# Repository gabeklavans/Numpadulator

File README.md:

# Numpadulator
 QMK powered numpad + calculator
 
 ## TODO:
 * Write (or borrow) C calculator code
 * Incorporate calculator into Numpadulator
 * ~~Build working prototype~~

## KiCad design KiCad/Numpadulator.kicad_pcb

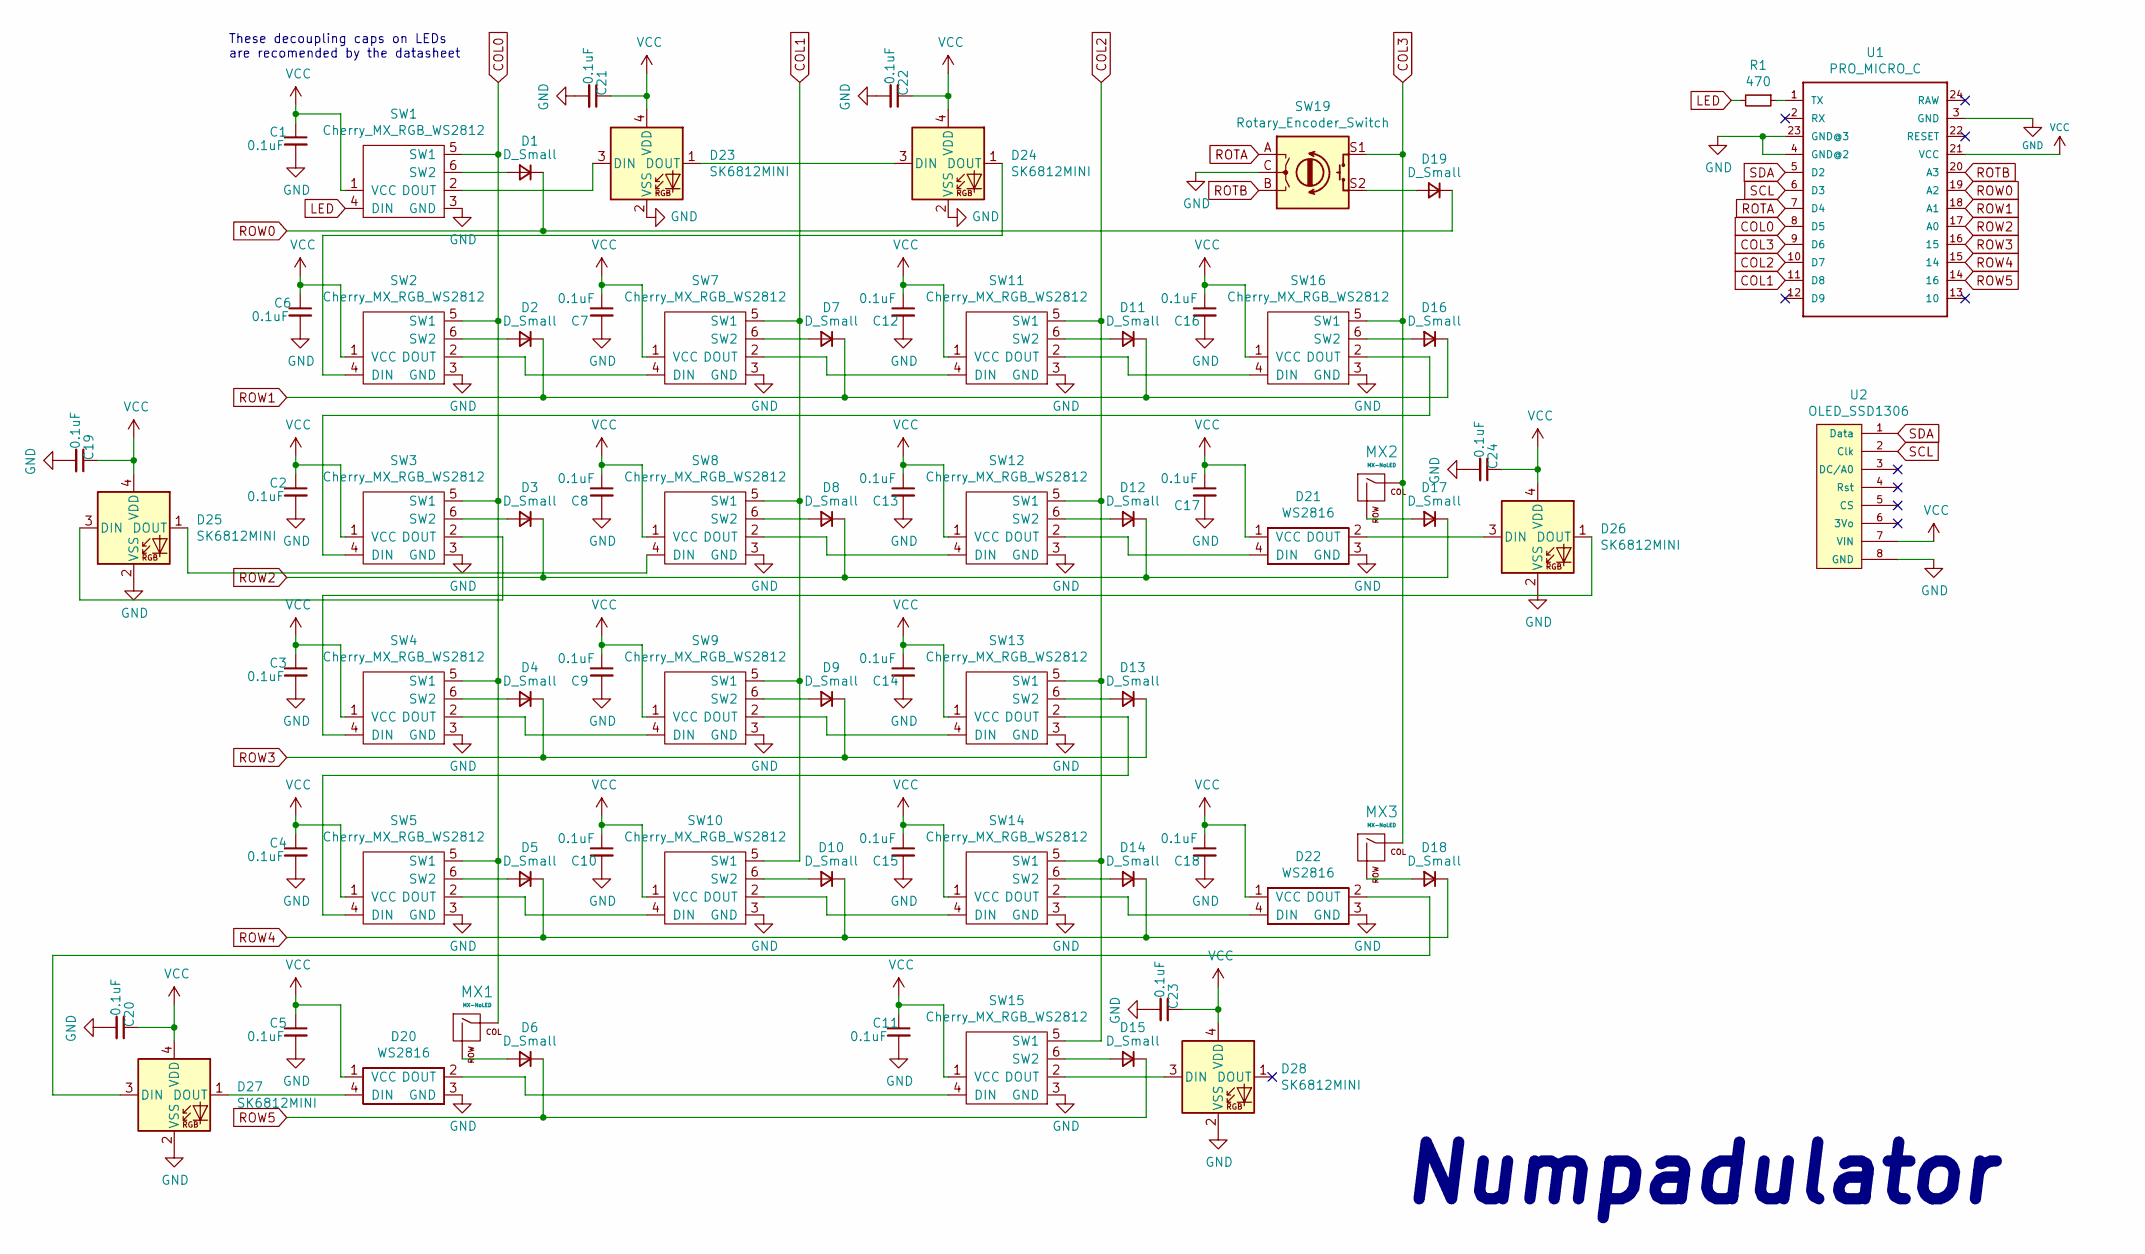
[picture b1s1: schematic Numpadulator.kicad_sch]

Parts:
C1, C2, C3, C4, C5, C6, C7, C8, C9, C10, C11, C12, C13, C14, C15, C16, C17, C18, C19, C20, C21, C22, C23, C24: 0.1uF; C_0805_2012Metric
D1, D2, D3, D4, D5, D6, D7, D8, D9, D10, D11, D12, D13, D14, D15, D16, D17, D18, D19: D_Small; D_SOD-123
D20, D21, D22: WS2816; SK6812-MINI-E
D23, D24, D25, D26, D27, D28: SK6812MINI; LED_SK6812MINI_PLCC4_3.5x3.5mm_P1.75mm
MX1, MX2, MX3: MX-NoLED; MXOnly-2U-Hotswap
R1: 470; R_0805_2012Metric
SW1, SW2, SW3, SW4, SW5, SW7, SW8, SW9, SW10, SW11, SW12, SW13, SW14, SW15, SW16: Cherry_MX_RGB_WS2812; Cherry-MX_PCB-Mounted_SK6812-MINI-E_Kailh_Socket
SW19: Rotary_Encoder_Switch; XDCR_PEC11R-4215F-S0024
U1: PRO_MICRO_C
U2: OLED_SSD1306; Adafruit_SSD1306

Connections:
COL0: MX1.1 (COL), SW1.5 (SW1), SW2.5 (SW1), SW3.5 (SW1), SW4.5 (SW1), SW5.5 (SW1), U1.8 (D5)
COL1: SW7.5 (SW1), SW8.5 (SW1), SW9.5 (SW1), SW10.5 (SW1), U1.11 (D8)
COL2: SW11.5 (SW1), SW12.5 (SW1), SW13.5 (SW1), SW14.5 (SW1), SW15.5 (SW1), U1.10 (D7)
COL3: MX2.1 (COL), MX3.1 (COL), SW16.5 (SW1), SW19.S1, U1.9 (D6)
GND: C1.2, C2.2, C3.2, C4.2, C5.2, C6.2, C7.2, C8.2, C9.2, C10.2, C11.2, C12.2, C13.2, C14.2, C15.2, C16.2, C17.2, C18.2, C19.2, C20.2, C21.2, C22.2, C23.2, C24.2, D20.3 (GND), D21.3 (GND), D22.3 (GND), D23.2 (VSS), D24.2 (VSS), D25.2 (VSS), D26.2 (VSS), D27.2 (VSS), D28.2 (VSS), SW1.3 (GND), SW2.3 (GND), SW3.3 (GND), SW4.3 (GND), SW5.3 (GND), SW7.3 (GND), SW8.3 (GND), SW9.3 (GND), SW10.3 (GND), SW11.3 (GND), SW12.3 (GND), SW13.3 (GND), SW14.3 (GND), SW15.3 (GND), SW16.3 (GND), SW19.C, U1.3 (GND), U1.4 (GND@2), U1.23 (GND@3), U2.8 (GND)
LED: R1.2, SW1.4 (DIN)
unnamed: D1.2 (A), SW1.6 (SW2)
unnamed: D2.2 (A), SW2.6 (SW2)
unnamed: D3.2 (A), SW3.6 (SW2)
unnamed: D4.2 (A), SW4.6 (SW2)
unnamed: D5.2 (A), SW5.6 (SW2)
unnamed: D6.2 (A), MX1.2 (ROW)
unnamed: D7.2 (A), SW7.6 (SW2)
unnamed: D8.2 (A), SW8.6 (SW2)
unnamed: D9.2 (A), SW9.6 (SW2)
unnamed: D10.2 (A), SW10.6 (SW2)
unnamed: D11.2 (A), SW11.6 (SW2)
unnamed: D12.2 (A), SW12.6 (SW2)
unnamed: D13.2 (A), SW13.6 (SW2)
unnamed: D14.2 (A), SW14.6 (SW2)
unnamed: D15.2 (A), SW15.6 (SW2)
unnamed: D16.2 (A), SW16.6 (SW2)
unnamed: D17.2 (A), MX2.2 (ROW)
unnamed: D18.2 (A), MX3.2 (ROW)
unnamed: D19.2 (A), SW19.S2
unnamed: D20.2 (DOUT), SW15.4 (DIN)
unnamed: D20.4 (DIN), D27.1 (DOUT)
unnamed: D21.2 (DOUT), D26.3 (DIN)
unnamed: D21.4 (DIN), SW12.2 (DOUT)
unnamed: D22.2 (DOUT), D27.3 (DIN)
unnamed: D22.4 (DIN), SW14.2 (DOUT)
unnamed: D23.1 (DOUT), D24.3 (DIN)
unnamed: D23.3 (DIN), SW1.2 (DOUT)
unnamed: D24.1 (DOUT), SW2.4 (DIN)
unnamed: D25.1 (DOUT), SW8.4 (DIN)
unnamed: D25.3 (DIN), SW3.2 (DOUT)
unnamed: D26.1 (DOUT), SW4.4 (DIN)
unnamed: D28.3 (DIN), SW15.2 (DOUT)
unnamed: R1.1, U1.1 (TX)
unnamed: SW2.2 (DOUT), SW7.4 (DIN)
unnamed: SW4.2 (DOUT), SW9.4 (DIN)
unnamed: SW10.2 (DOUT), SW14.4 (DIN)
unnamed: SW5.2 (DOUT), SW10.4 (DIN)
unnamed: SW11.2 (DOUT), SW16.4 (DIN)
unnamed: SW7.2 (DOUT), SW11.4 (DIN)
unnamed: SW8.2 (DOUT), SW12.4 (DIN)
unnamed: SW5.4 (DIN), SW13.2 (DOUT)
unnamed: SW9.2 (DOUT), SW13.4 (DIN)
unnamed: SW3.4 (DIN), SW16.2 (DOUT)
ROTA: SW19.A, U1.7 (D4)
ROTB: SW19.B, U1.20 (A3)
ROW0: D1.1 (K), D19.1 (K), U1.19 (A2)
ROW1: D2.1 (K), D7.1 (K), D11.1 (K), D16.1 (K), U1.18 (A1)
ROW2: D3.1 (K), D8.1 (K), D12.1 (K), D17.1 (K), U1.17 (A0)
ROW3: D4.1 (K), D9.1 (K), D13.1 (K), U1.16 (15)
ROW4: D5.1 (K), D10.1 (K), D14.1 (K), D18.1 (K), U1.15 (14)
ROW5: D6.1 (K), D15.1 (K), U1.14 (16)
SCL: U1.6 (D3), U2.2 (Clk)
SDA: U1.5 (D2), U2.1 (Data)
VCC: C1.1, C2.1, C3.1, C4.1, C5.1, C6.1, C7.1, C8.1, C9.1, C10.1, C11.1, C12.1, C13.1, C14.1, C15.1, C16.1, C17.1, C18.1, C19.1, C20.1, C21.1, C22.1, C23.1, C24.1, D20.1 (VCC), D21.1 (VCC), D22.1 (VCC), D23.4 (VDD), D24.4 (VDD), D25.4 (VDD), D26.4 (VDD), D27.4 (VDD), D28.4 (VDD), SW1.1 (VCC), SW2.1 (VCC), SW3.1 (VCC), SW4.1 (VCC), SW5.1 (VCC), SW7.1 (VCC), SW8.1 (VCC), SW9.1 (VCC), SW10.1 (VCC), SW11.1 (VCC), SW12.1 (VCC), SW13.1 (VCC), SW14.1 (VCC), SW15.1 (VCC), SW16.1 (VCC), U1.21 (VCC), U2.7 (VIN)

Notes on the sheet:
Numpadulator
These decoupling caps on LEDs are recomended by the datasheet

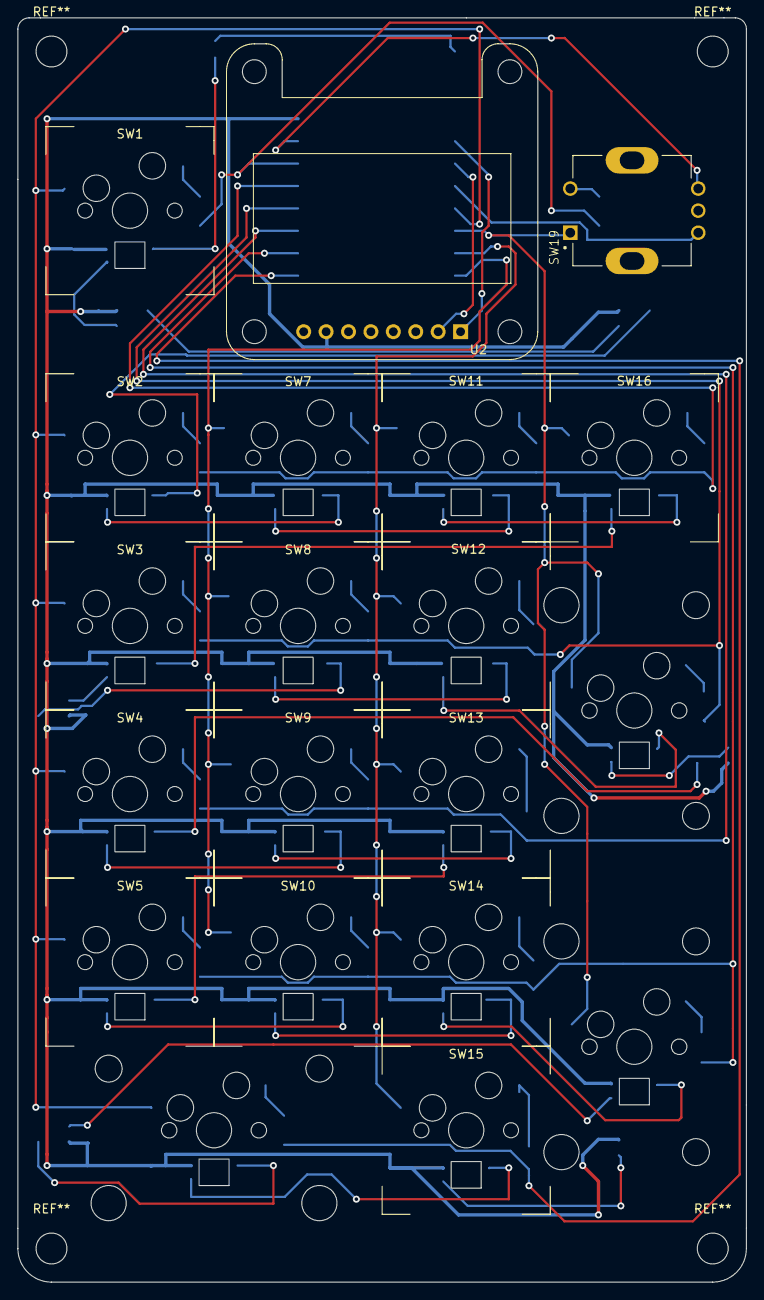
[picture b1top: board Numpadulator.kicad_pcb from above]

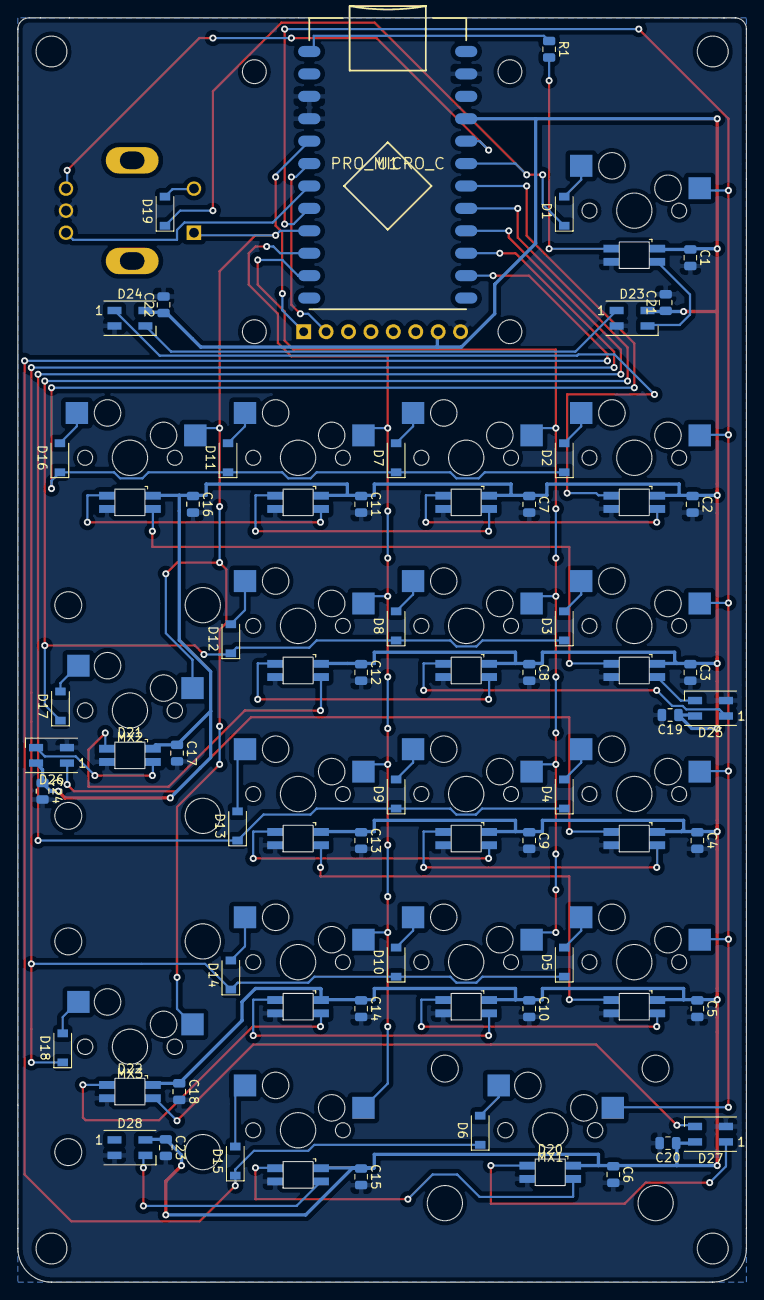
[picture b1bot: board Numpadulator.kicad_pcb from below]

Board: 2 copper layers, 82.5 x 143.3 mm, 74 parts (51 on the bottom side), 60 nets.

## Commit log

2020-07-24 Project creation
2020-07-24 Added sparkfun lib
2020-07-24 Added sf eagle libs
2020-07-24 Added libs/footprints, threw pro into schematic
2020-07-24 Cleanup
2020-07-25 Update fp-info-cache
2020-07-25 Added MX breakout board submodule
2020-07-25 Made rbg symbol for ws2812
2020-07-26 Added custom lib with new mx hotswap w/ cutout
2020-07-26 Added back mx breakout and removed default fp on pro micro
2020-07-26 Moved files to KiCad folder
2020-07-26 Moved back readme
2020-07-26 Dropped in RotEnc and hooked up OLED
2020-07-29 Added matrix w/o power
2020-07-29 Started to make look better
2020-07-29 Added targetting silk to mx footprint
    also threw in footprint for my rotary encoder
2020-07-29 Reworked main matrix schem
2020-07-29 A little cleanup
2020-07-29 Started fleshing out pcb, need to change large keys
2020-07-30 Threw in some standard MX libs
2020-07-30 Updated new combined mx led footprint
2020-07-30 More layout and frustration 3:
2020-07-30 Laid out PCB
2020-07-30 Better PCB layout
2020-08-09 Moved MCU via the Genius of WIll
2020-10-28 Pic and fusion360 proj file
2020-10-28 Added some pics
2020-10-28 This is in fact, a WIP
2021-01-02 Traced edge cuts
2021-01-05 cache update
2021-01-05 add some power to the caps
2021-01-06 started some LED routing
2021-01-07 added some whack wiring for LEDs and some Columns
2021-01-30 Added tracks up to the rows and random shit
2021-01-31 Actually aligned some stuff
2021-01-31 literally nudged the top two up so slightly wow
2021-01-31 nudge track
2021-01-31 Actually made the thing symmetric
2021-01-31 fixed track
2021-01-31 flipped top right 1.5u. now the bottom right...
2021-01-31 flipped the side 1.5us. ugh.
2021-01-31 update step file
2021-02-02 Wired up rows, realized there is something wrong with the 2u keys rows in the schematic...
2021-02-05 generate gerbs and pos plots
2021-02-12 Switched + and return to be in right order and orientation...also maybe finished routing??
2021-02-12 FINISHED THE WIRING except now I need to add the underglow LEDs...
2021-02-12 add resistor coming from LED pin
2021-02-14 Some new renders
2021-02-14 Update fusion archive file
2021-02-14 Rename?
2021-02-14 got underglow LEDs in schematic... gotta wire them up now
2021-02-14 forgot to save
2021-03-03 PLACED EVERYTHING I THINK
2021-03-03 made some GND SPACE
2021-03-03 now.. they should be placed right... maybe...
2021-03-03 jk for real this time lololol
2021-03-03 10,000th times the charm!
2021-03-03 I crave... something
2021-03-03 lolol
2021-03-03 it.. might be done now???!?
2021-03-03 made gerbs and fixed buggs
2021-03-03 updated gerbers
2021-03-07 made it... holier
2021-04-20 Delete .DS_Store
    Thanks MacOS
2022-04-06 Add some aux files
2022-04-06 add fancy gif
2022-04-06 Add demo gif and TODOs to README
2022-04-06 Reduce gif size + quality
2022-04-06 Convert schematic and pcb to KiCad 6
